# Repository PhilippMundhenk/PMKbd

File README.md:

# PMKbd
A fully wireless split Bluetooth keyboard, a new creation with design based on [crkbd](https://github.com/foostan/crkbd) and connectivity based on [mitosis](https://www.reddit.com/r/MechanicalKeyboards/comments/66588f/wireless_split_qmk_mitosis/) ([hardware](https://github.com/reversebias/mitosis-hardware), [software](https://github.com/reversebias/mitosis)). Some final touches by myself.

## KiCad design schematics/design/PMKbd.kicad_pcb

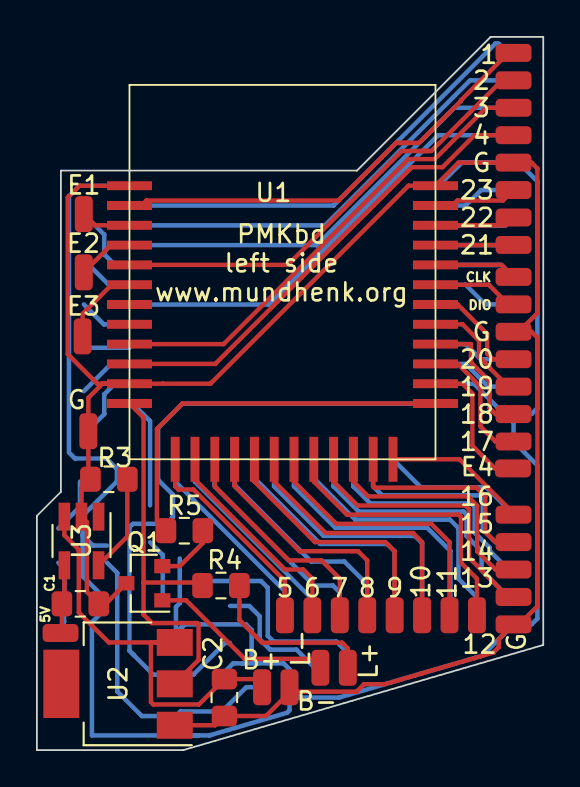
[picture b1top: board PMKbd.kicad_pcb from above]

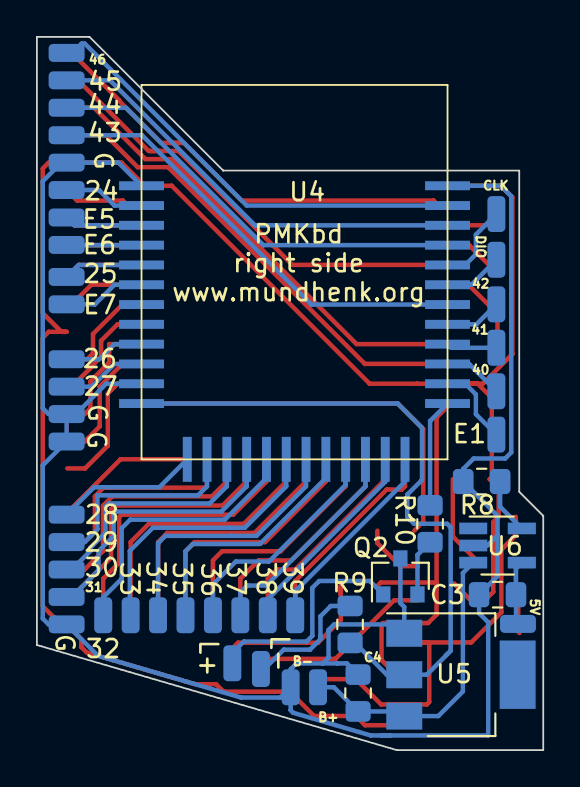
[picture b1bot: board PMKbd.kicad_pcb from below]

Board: 2 copper layers, 28.1 x 39.6 mm, 94 parts (47 on the bottom side), 76 nets.

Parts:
1, 2, 3, 4, 5, 5V, 5V#2, 6, 7, 8, 9, 10, 11, 12, 13, 14, 15, 16, 17, 18, 19, 20, 21, 22, 23, 24, 25, 26, 27, 28, 29, 30, 31, 32, 33, 34, 35, 36, 37, 38, 39, 40, 41, 42, 43, 44, 45, 46: Conn_01x01; SolderWirePad_1x01_SMD_1x2mm
B+: Conn_01x01; SolderWirePad_1x01_SMD_1x2mm
B+#2: Conn_01x01; SolderWirePad_1x01_SMD_1x2mm
B-: Conn_01x01; SolderWirePad_1x01_SMD_1x2mm
B-#2: Conn_01x01; SolderWirePad_1x01_SMD_1x2mm
C1, C2, C3, C4: 10µF; C_0805_2012Metric_Pad1.15x1.40mm_HandSolder
CLK: Conn_01x01; SolderWirePad_1x01_SMD_1x2mm
CLK#2: Conn_01x01; SolderWirePad_1x01_SMD_1x2mm
DIO: Conn_01x01; SolderWirePad_1x01_SMD_1x2mm
DIO#2: Conn_01x01; SolderWirePad_1x01_SMD_1x2mm
E1, E1#2, E2, E3, E4, E5, E6, E7: Conn_01x01; SolderWirePad_1x01_SMD_1x2mm
G: Conn_01x01; SolderWirePad_1x01_SMD_1x2mm
G#2, G#3, G#4, G#5, G#6, G#7, G#8: Conn_01x01; SolderWirePad_1x01_SMD_1x2mm
L+: Conn_01x01; SolderWirePad_1x01_SMD_1x2mm
L+#2: Conn_01x01; SolderWirePad_1x01_SMD_1x2mm
L-: Conn_01x01; SolderWirePad_1x01_SMD_1x2mm
L-#2: Conn_01x01; SolderWirePad_1x01_SMD_1x2mm
Q1, Q2: 2N2222; SOT-23
R3, R5, R8, R10: 10K; R_0805_2012Metric_Pad1.15x1.40mm_HandSolder
R4, R9: 200; R_0805_2012Metric_Pad1.15x1.40mm_HandSolder
U1, U4: Core51822_(B)
U2, U5: LT1117-3.3; SOT-223
U3, U6: MCP73831-2-OT; SOT-23-5_HandSoldering

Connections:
3.3V_L: R4.2, U1.12, U2.2
3.3V_R: R9.2, U4.12, U5.2
5V_L: 5V#2.1, C1.1, U3.4
5V_R: 5V.1, C3.1, U6.4
EXT1: E1.1, U1.3
EXT2: E2.1, U1.4
EXT3: E3.1, U1.6
EXT4: E4.1, U1.26
EXT5: E5.1, U4.3
EXT6: E6.1, U4.4
EXT7: E7.1, U4.6
EXT8: E1#2.1, U4.26
GND_L: B-.1, C1.2, C2.2, G#5.1, G#6.1, G#7.1, G#8.1, Q1.3, R3.1, U1.1, U1.11, U1.36, U2.1, U3.2
GND_R: B-#2.1, C3.2, C4.2, G.1, G#2.1, G#3.1, G#4.1, Q2.3, R8.1, U4.1, U4.11, U4.36, U5.1, U6.2
LED_L: R5.1, U1.25
LED_R: R10.1, U4.25
unnamed: B+#2.1, C2.1, U2.3, U3.3
unnamed: B+.1, C4.1, U5.3, U6.3
unnamed: L+.1, R4.1
unnamed: L-#2.1, Q1.1
unnamed: CLK#2.1, U1.32
unnamed: DIO#2.1, U1.31
unnamed: L-.1, R9.1
unnamed: L+#2.1, Q2.1
unnamed: CLK.1, U4.32
unnamed: DIO.1, U4.31
unnamed: Q1.2, R5.2
unnamed: Q2.2, R10.2
unnamed: R3.2, U3.5
unnamed: R8.2, U6.5
S1: 1.1, U1.2
S2: 2.1, U1.5
S3: 3.1, U1.9
S4: 4.1, U1.10
S5: 5.1, U1.13
S6: 6.1, U1.14
S7: 7.1, U1.15
S8: 8.1, U1.16
S9: 9.1, U1.17
S10: 10.1, U1.18
S11: 11.1, U1.19
S12: 12.1, U1.20
S13: 13.1, U1.21
S14: 14.1, U1.22
S15: 15.1, U1.23
S16: 16.1, U1.24
S17: 17.1, U1.27
S18: 18.1, U1.28
S19: 19.1, U1.29
S20: 20.1, U1.30
S21: 21.1, U1.33
S22: 22.1, U1.34
S23: 23.1, U1.35
S24: 24.1, U4.2
S25: 25.1, U4.5
S26: 26.1, U4.9
S27: 27.1, U4.10
S28: 28.1, U4.13
S29: 29.1, U4.14
S30: 30.1, U4.15
S31: 31.1, U4.16
S32: 32.1, U4.17
S33: 33.1, U4.18
S34: 34.1, U4.19
S35: 35.1, U4.20
S36: 36.1, U4.21
S37: 37.1, U4.22
S38: 38.1, U4.23
S39: 39.1, U4.24
S40: 40.1, U4.27
S41: 41.1, U4.28
S42: 42.1, U4.29
S43: 43.1, U4.30
S44: 44.1, U4.33
S45: 45.1, U4.34
S46: 46.1, U4.35

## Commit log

2020-12-11 short description added
2020-12-11 reassociating...
2020-12-11 manually annotated
2020-12-11 annotated more
2020-12-11 fixed references
2020-12-11 added EXT pads
2020-12-12 optimized, missing lib added
2020-12-12 optimized more
2020-12-12 minor changes
2020-12-12 first time right and left layouted
2020-12-12 minimal improvements
2020-12-14 inital version of case added
2020-12-14 case finalized
2020-12-15 finalized PCB
2021-01-01 added right side
